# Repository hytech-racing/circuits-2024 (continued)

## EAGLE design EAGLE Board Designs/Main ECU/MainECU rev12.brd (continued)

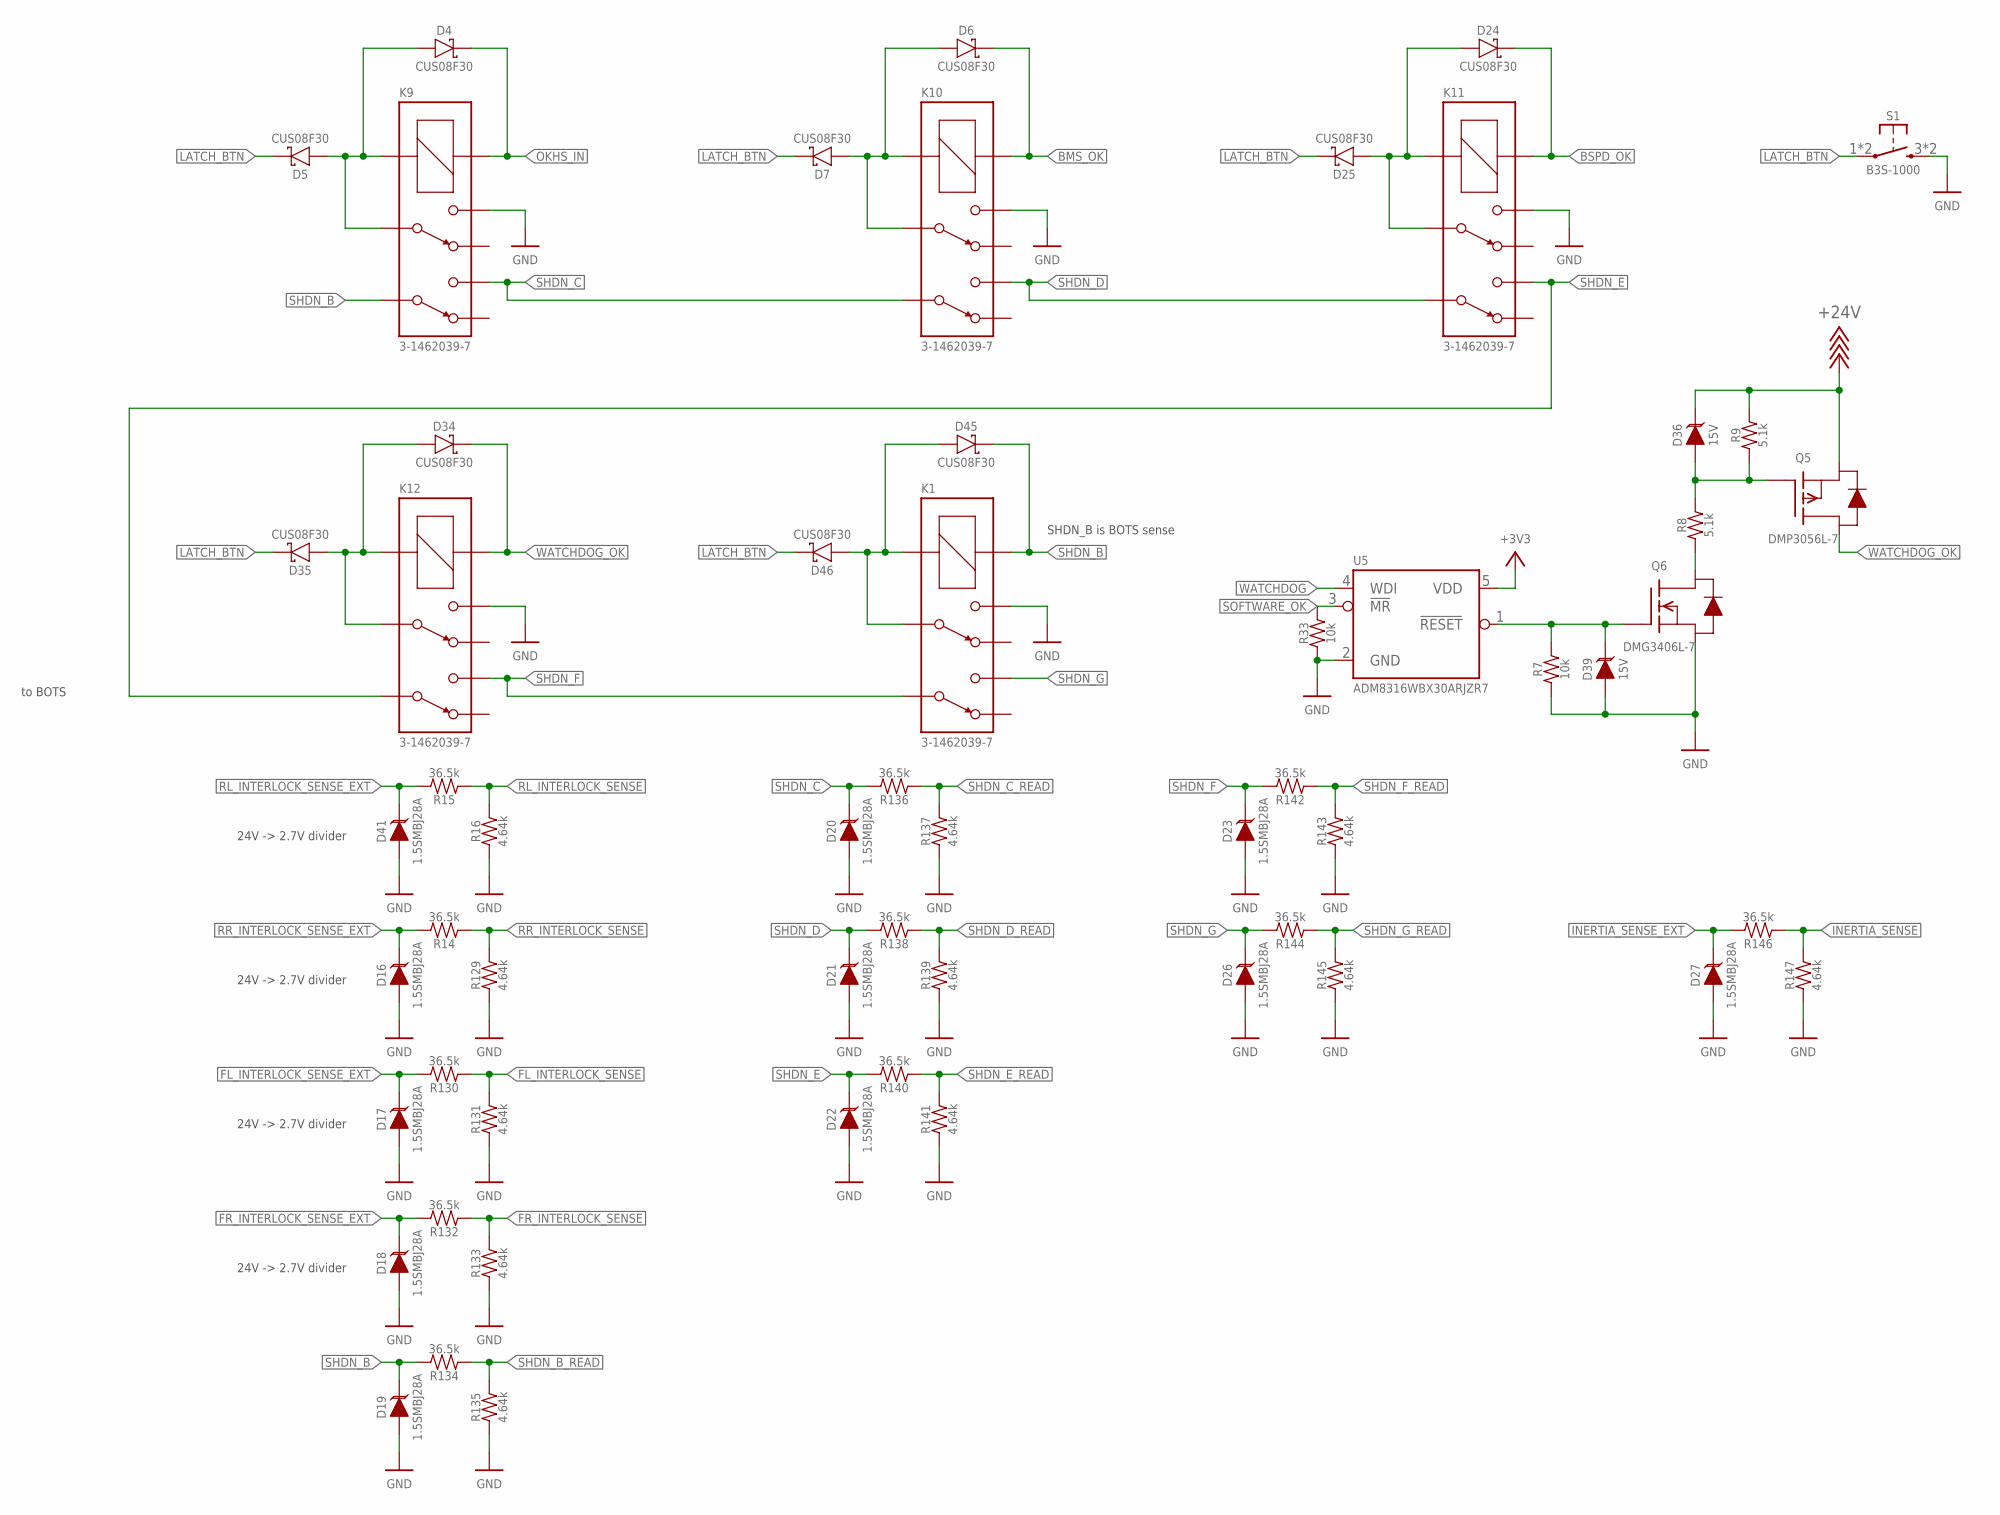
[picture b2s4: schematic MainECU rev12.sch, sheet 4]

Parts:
D4, D5, D6, D7, D24, D25, D34, D35, D45, D46: SCHOTTKY_SOD323_30V; SOD-323
D16, D17, D18, D19, D20, D21, D22, D23, D26, D27, D41: TVS_DO-214AA_28V; DO-214AA
D36, D39: TVS__15V; SOT-23
K1, K9, K10, K11, K12: RELAY_DPDT_07DSMT; IM*G
Q5: TRANSISTOR_P_MOS_SOT-23_DMP3056L-7; SOT-23
Q6: TRANSISTOR_N_MOS__DMG3406L-7; SOT-23
R7, R33: RESISTOR_0603_10K; 0603-RES
R8, R9: RESISTOR_0603_5.1K; 0603-RES
R14, R15, R130, R132, R134, R136, R138, R140, R142, R144, R146: RESISTOR_0603_36.5K; 0603-RES
R16, R129, R131, R133, R135, R137, R139, R141, R143, R145, R147: RESISTOR_0603_4.64K; 0603-RES
S1: BUTTON; B3S-100X
U5: ADM8316WBX30; SOT-23-5

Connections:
+3V3: U5.5 (VDD); also elsewhere on the board
+24V: D36.3 (C), Q5.2 (S), R9.2; also elsewhere on the board
BMS_OK: D6.C, K10.1 (COIL+); also elsewhere on the board
BSPD_OK: D24.C, K11.1 (COIL+); also elsewhere on the board
FL_INTERLOCK_SENSE: R130.1, R131.2; also elsewhere on the board
FL_INTERLOCK_SENSE_EXT: D17.2 (C), R130.2; also elsewhere on the board
FR_INTERLOCK_SENSE: R132.1, R133.2; also elsewhere on the board
FR_INTERLOCK_SENSE_EXT: D18.2 (C), R132.2; also elsewhere on the board
GND: D16.1 (A), D17.1 (A), D18.1 (A), D19.1 (A), D20.1 (A), D21.1 (A), D22.1 (A), D23.1 (A), D26.1 (A), D27.1 (A), D39.1 (A), D41.1 (A), K1.4, K9.4, K10.4, K11.4, K12.4, Q6.2 (S), R7.1, R16.1, R33.1, R129.1, R131.1, R133.1, R135.1, R137.1, R139.1, R141.1, R143.1, R145.1, R147.1, S1.3 (S), S1.4 (S), U5.2 (GND); also elsewhere on the board
INERTIA_SENSE: R146.1, R147.2; also elsewhere on the board
INERTIA_SENSE_EXT: D27.2 (C), R146.2; also elsewhere on the board
LATCH_BTN: D5.C, D7.C, D25.C, D35.C, D46.C, S1.1, S1.2; also elsewhere on the board
unnamed: D36.1 (A), Q5.1 (G), R8.2, R9.1
unnamed: Q6.3 (D), R8.1
unnamed: D4.A, D5.A, K9.3, K9.8 (COIL-)
unnamed: D24.A, D25.A, K11.3, K11.8 (COIL-)
unnamed: D6.A, D7.A, K10.3, K10.8 (COIL-)
unnamed: D45.A, D46.A, K1.3, K1.8 (COIL-)
unnamed: D34.A, D35.A, K12.3, K12.8 (COIL-)
OKHS_IN: D4.C, K9.1 (COIL+); also elsewhere on the board
RL_INTERLOCK_SENSE: R15.1, R16.2; also elsewhere on the board
RL_INTERLOCK_SENSE_EXT: D41.2 (C), R15.2; also elsewhere on the board
RR_INTERLOCK_SENSE: R14.1, R129.2; also elsewhere on the board
RR_INTERLOCK_SENSE_EXT: D16.2 (C), R14.2; also elsewhere on the board
SHDN_B: D19.2 (C), D45.C, K1.1 (COIL+), K9.6, R134.2; also elsewhere on the board
SHDN_B_READ: R134.1, R135.2; also elsewhere on the board
SHDN_C: D20.2 (C), K9.5, K10.6, R136.2; also elsewhere on the board
SHDN_C_READ: R136.1, R137.2; also elsewhere on the board
SHDN_D: D21.2 (C), K10.5, K11.6, R138.2; also elsewhere on the board
SHDN_D_READ: R138.1, R139.2; also elsewhere on the board
SHDN_E: D22.2 (C), K11.5, K12.6, R140.2; also elsewhere on the board
SHDN_E_READ: R140.1, R141.2; also elsewhere on the board
SHDN_F: D23.2 (C), K1.6, K12.5, R142.2; also elsewhere on the board
SHDN_F_READ: R142.1, R143.2; also elsewhere on the board
SHDN_G: D26.2 (C), K1.5, R144.2; also elsewhere on the board
SHDN_G_READ: R144.1, R145.2; also elsewhere on the board
SOFTWARE_OK: R33.2, U5.3 (!MR!); also elsewhere on the board
WATCHDOG: U5.4 (WDI); also elsewhere on the board
WATCHDOG_OK: D34.C, K12.1 (COIL+), Q5.3 (D); also elsewhere on the board
WATCHDOG_OK_LV: D39.3 (C), Q6.1 (G), R7.2, U5.1 (!RESET!)

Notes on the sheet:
to BOTS
24V -> 2.7V divider
SHDN_B is BOTS sense

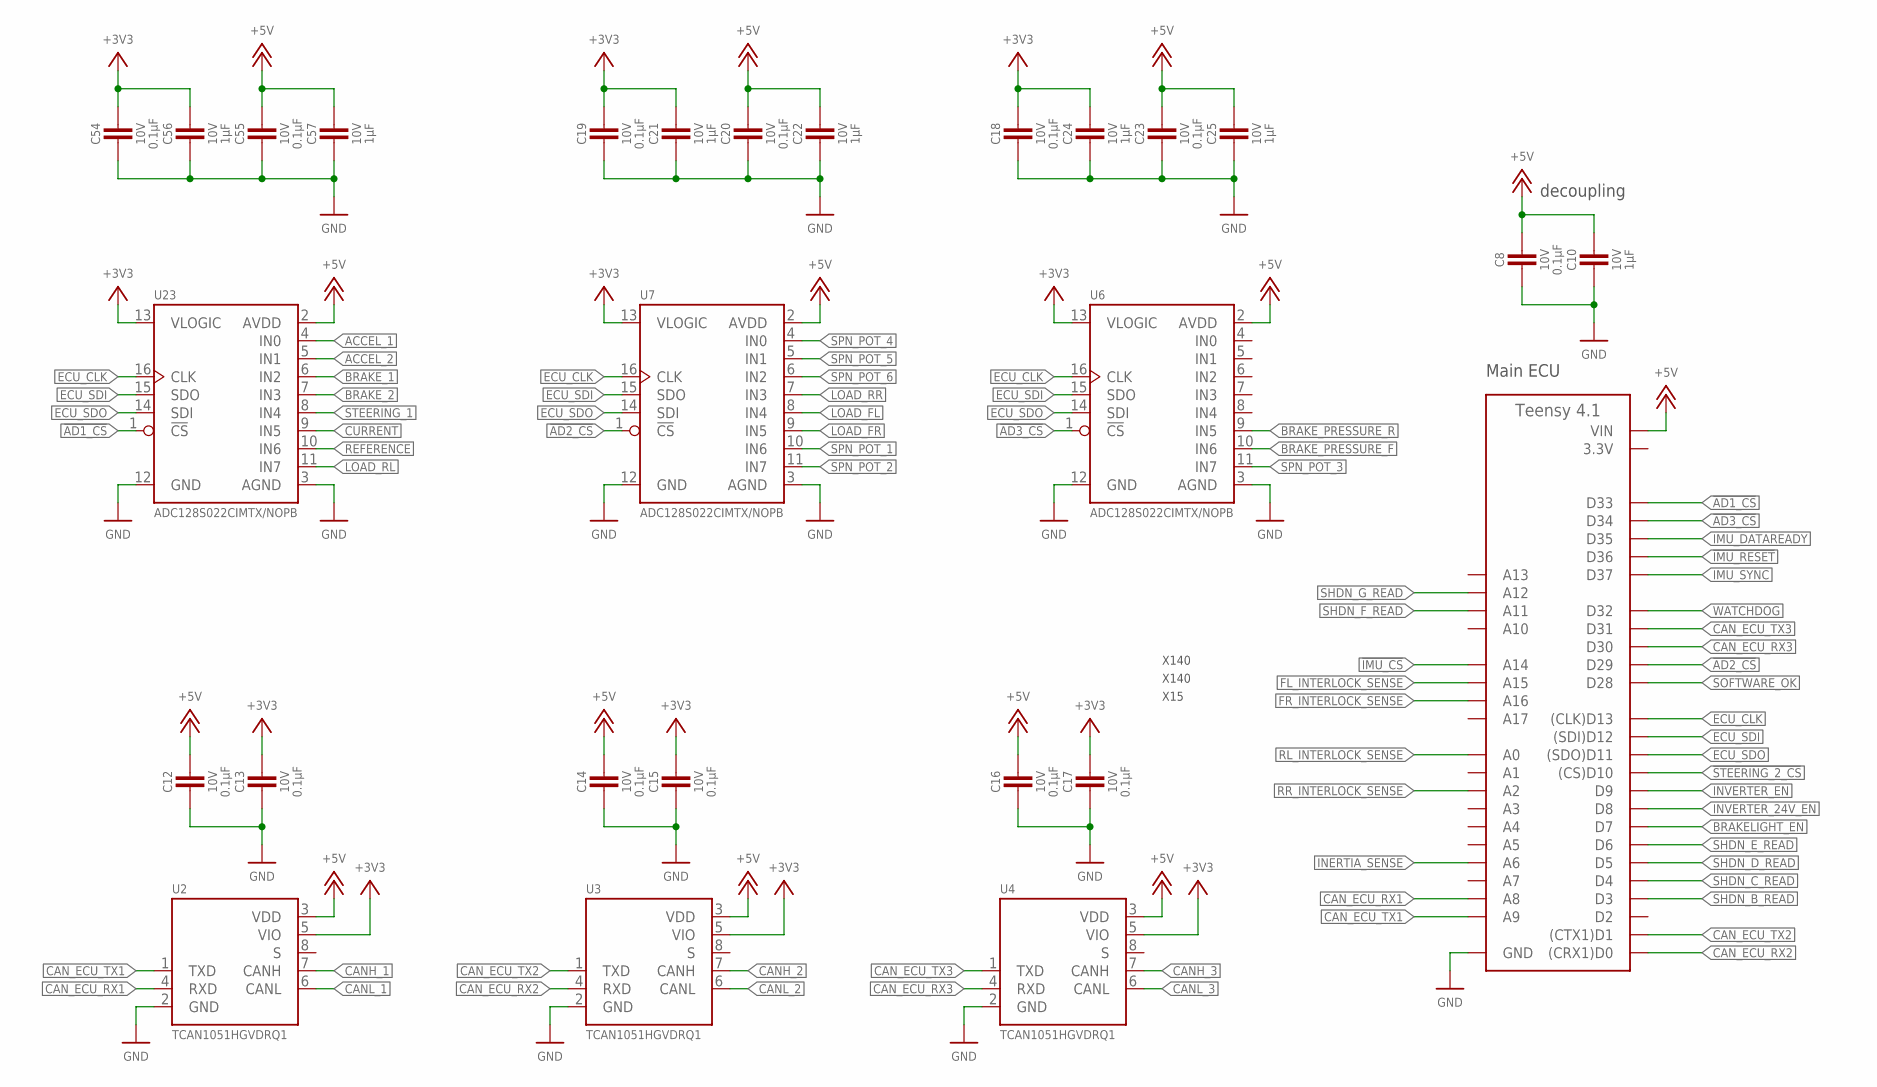
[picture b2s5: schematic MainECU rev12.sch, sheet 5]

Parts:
A2: TEENSY_4.1_SMT; TEENSY_LONG_SSM
C8, C12, C13, C14, C15, C16, C17, C18, C19, C20, C23, C54, C55: CAPACITOR_0603_10V_0.1UF; 0603-CAP
C10, C21, C22, C24, C25, C56, C57: CAPACITOR_0603_10V_1UF; 0603-CAP
U2, U3, U4: TCAN1051HQV-Q1; SOIC-08(NARROW,0.15")
U6, U7, U23: ADC128S022; TSSOP-16

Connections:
3.3V: A2.3.3V, A2.3.3V@1 (3.3V); also elsewhere on the board
!AD1_CS: A2.D33, U23.1 (!CS!)
!AD2_CS: A2.D29, U7.1 (!CS!)
!AD3_CS: A2.D34, U6.1 (!CS!)
!IMU_CS: A2.D38 (A14); also elsewhere on the board
!IMU_RESET: A2.D36; also elsewhere on the board
!STEERING_2_CS: A2.D10 ((CS)D10); also elsewhere on the board
+3V3: C13.1, C15.1, C17.1, C18.1, C19.1, C21.1, C24.1, C54.1, C56.1, U2.5 (VIO), U3.5 (VIO), U4.5 (VIO), U6.13 (VLOGIC), U7.13 (VLOGIC), U23.13 (VLOGIC); also elsewhere on the board
+5V: A2.VIN, C8.1, C10.1, C12.1, C14.1, C16.1, C20.1, C22.1, C23.1, C25.1, C55.1, C57.1, U2.3 (VDD), U3.3 (VDD), U4.3 (VDD), U6.2 (AVDD), U7.2 (AVDD), U23.2 (AVDD); also elsewhere on the board
ACCEL_1: U23.4 (IN0); also elsewhere on the board
ACCEL_2: U23.5 (IN1); also elsewhere on the board
BRAKELIGHT_EN: A2.D7; also elsewhere on the board
BRAKE_1: U23.6 (IN2); also elsewhere on the board
BRAKE_2: U23.7 (IN3); also elsewhere on the board
BRAKE_PRESSURE_F: U6.10 (IN6); also elsewhere on the board
BRAKE_PRESSURE_R: U6.9 (IN5); also elsewhere on the board
CANH_1: U2.7 (CANH); also elsewhere on the board
CANH_2: U3.7 (CANH); also elsewhere on the board
CANH_3: U4.7 (CANH); also elsewhere on the board
CANL_1: U2.6 (CANL); also elsewhere on the board
CANL_2: U3.6 (CANL); also elsewhere on the board
CANL_3: U4.6 (CANL); also elsewhere on the board
CAN_ECU_RX1: A2.D22 (A8), U2.4 (RXD)
CAN_ECU_RX2: A2.D0 ((CRX1)D0), U3.4 (RXD)
CAN_ECU_RX3: A2.D30, U4.4 (RXD)
CAN_ECU_TX1: A2.D23 (A9), U2.1 (TXD)
CAN_ECU_TX2: A2.D1 ((CTX1)D1), U3.1 (TXD)
CAN_ECU_TX3: A2.D31, U4.1 (TXD)
CURRENT: U23.9 (IN5); also elsewhere on the board
ECU_CLK: A2.D13 ((CLK)D13), U6.16 (CLK), U7.16 (CLK), U23.16 (CLK); also elsewhere on the board
ECU_SDI: A2.D12 ((SDI)D12), U6.15 (SDO), U7.15 (SDO), U23.15 (SDO); also elsewhere on the board
ECU_SDO: A2.D11 ((SDO)D11), U6.14 (SDI), U7.14 (SDI), U23.14 (SDI); also elsewhere on the board
FL_INTERLOCK_SENSE: A2.D39 (A15); also elsewhere on the board
FR_INTERLOCK_SENSE: A2.D40 (A16); also elsewhere on the board
GND: A2.AGND/GND (GND), A2.GND, A2.GND@1 (GND), C8.2, C10.2, C12.2, C13.2, C14.2, C15.2, C16.2, C17.2, C18.2, C19.2, C20.2, C21.2, C22.2, C23.2, C24.2, C25.2, C54.2, C55.2, C56.2, C57.2, U2.2 (GND), U3.2 (GND), U4.2 (GND), U6.3 (AGND), U6.12 (GND), U7.3 (AGND), U7.12 (GND), U23.3 (AGND), U23.12 (GND); also elsewhere on the board
IMU_DATAREADY: A2.D35; also elsewhere on the board
IMU_SYNC: A2.D37; also elsewhere on the board
INERTIA_SENSE: A2.D20 (A6); also elsewhere on the board
INVERTER_24V_EN: A2.D8; also elsewhere on the board
INVERTER_EN: A2.D9; also elsewhere on the board
LOAD_FL: U7.8 (IN4); also elsewhere on the board
LOAD_FR: U7.9 (IN5); also elsewhere on the board
LOAD_RL: U23.11 (IN7); also elsewhere on the board
LOAD_RR: U7.7 (IN3); also elsewhere on the board
REFERENCE: U23.10 (IN6); also elsewhere on the board
RL_INTERLOCK_SENSE: A2.D14 (A0); also elsewhere on the board
RR_INTERLOCK_SENSE: A2.D16 (A2); also elsewhere on the board
SHDN_B_READ: A2.D3; also elsewhere on the board
SHDN_C_READ: A2.D4; also elsewhere on the board
SHDN_D_READ: A2.D5; also elsewhere on the board
SHDN_E_READ: A2.D6; also elsewhere on the board
SHDN_F_READ: A2.D25 (A11); also elsewhere on the board
SHDN_G_READ: A2.D26 (A12); also elsewhere on the board
SOFTWARE_OK: A2.D28; also elsewhere on the board
SPN_POT_1: U7.10 (IN6); also elsewhere on the board
SPN_POT_2: U7.11 (IN7); also elsewhere on the board
SPN_POT_3: U6.11 (IN7); also elsewhere on the board
SPN_POT_4: U7.4 (IN0); also elsewhere on the board
SPN_POT_5: U7.5 (IN1); also elsewhere on the board
SPN_POT_6: U7.6 (IN2); also elsewhere on the board
STEERING_1: U23.8 (IN4); also elsewhere on the board
WATCHDOG: A2.D32; also elsewhere on the board

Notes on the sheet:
decoupling
Main ECU
X15
X140

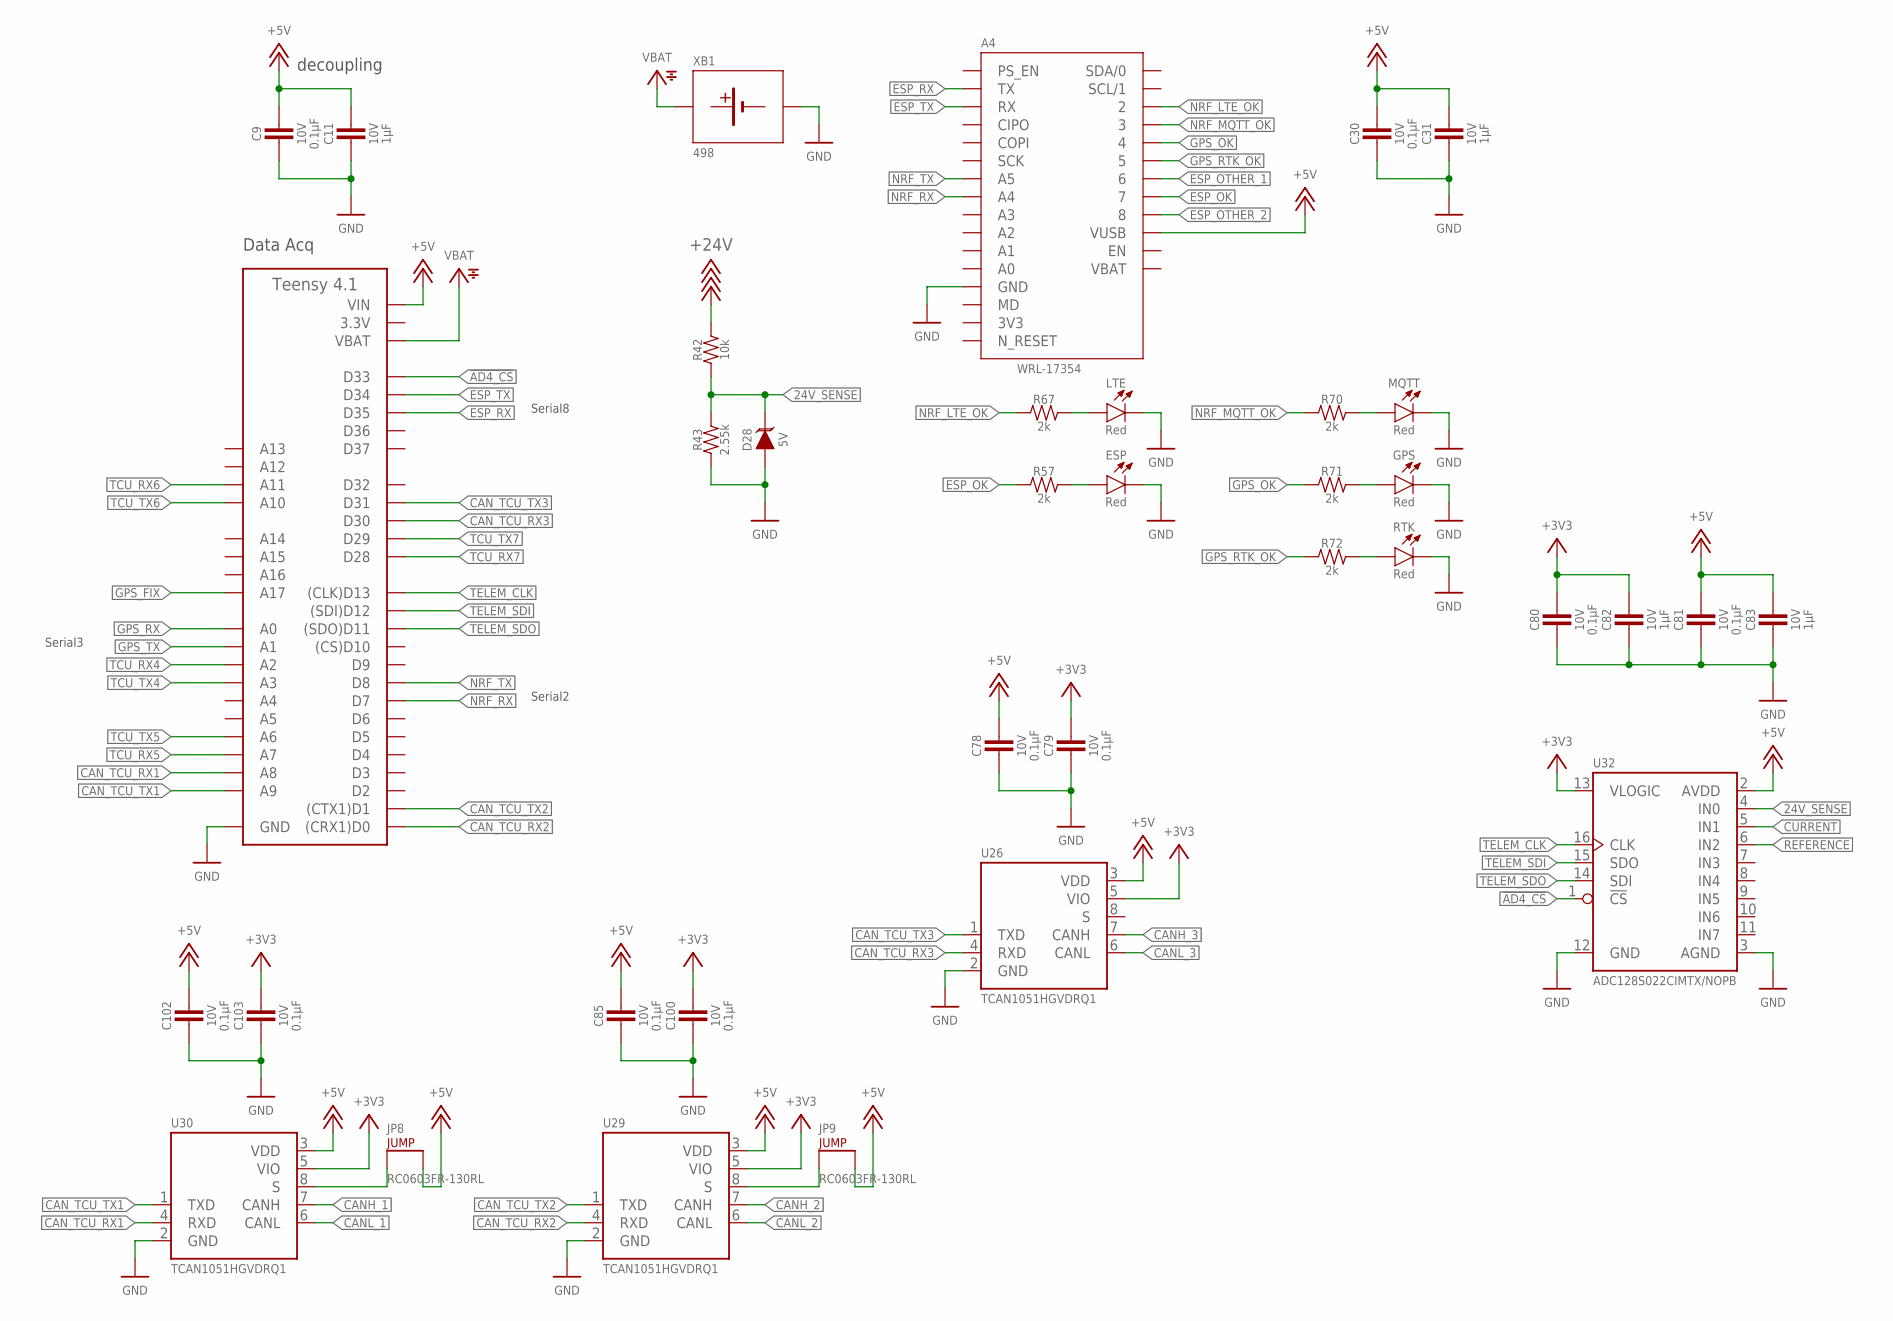
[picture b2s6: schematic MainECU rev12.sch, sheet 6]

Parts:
A3: TEENSY_4.1; TEENSY_LONG_EXT
A4: NRF9160LTE
C9, C30, C78, C79, C80, C81, C85, C100, C102, C103: CAPACITOR_0603_10V_0.1UF; 0603-CAP
C11, C31, C82, C83: CAPACITOR_0603_10V_1UF; 0603-CAP
D28: TVS__5V; SOT-23
ESP: LED_0603_RED; 0603-LED
GPS: LED_0603_RED; 0603-LED
JP8, JP9: JUMPER_0603_; 0603-RES
LTE: LED_0603_RED; 0603-LED
MQTT: LED_0603_RED; 0603-LED
R42: RESISTOR_0603_10K; 0603-RES
R43: RESISTOR_0603_2.55K; 0603-RES
R57, R67, R70, R71, R72: RESISTOR_0603_2K; 0603-RES
RTK: LED_0603_RED; 0603-LED
U26, U29, U30: TCAN1051HQV-Q1; SOIC-08(NARROW,0.15")
U32: ADC128S022; TSSOP-16
XB1: BATTERY_HOLDER_KEYSTONE_498; 498

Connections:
3.3V: A3.3V3 (3.3V), A3.3V3@2 (3.3V), A3.3V3@3 (3.3V); also elsewhere on the board
3V3: A4.3V3
24V_SENSE: D28.3 (C), R42.1, R43.2, U32.4 (IN0)
!AD4_CS: A3.D33, U32.1 (!CS!)
+3V3: C79.1, C80.1, C82.1, C100.1, C103.1, U26.5 (VIO), U29.5 (VIO), U30.5 (VIO), U32.13 (VLOGIC); also elsewhere on the board
+5V: A3.VIN, A4.VUSB, C9.1, C11.1, C30.1, C31.1, C78.1, C81.1, C83.1, C85.1, C102.1, JP8.2, JP9.2, U26.3 (VDD), U29.3 (VDD), U30.3 (VDD), U32.2 (AVDD); also elsewhere on the board
+24V: R42.2; also elsewhere on the board
CANH_1: U30.7 (CANH); also elsewhere on the board
CANH_2: U29.7 (CANH); also elsewhere on the board
CANH_3: U26.7 (CANH); also elsewhere on the board
CANL_1: U30.6 (CANL); also elsewhere on the board
CANL_2: U29.6 (CANL); also elsewhere on the board
CANL_3: U26.6 (CANL); also elsewhere on the board
CAN_TCU_RX1: A3.D22 (A8), U30.4 (RXD)
CAN_TCU_RX2: A3.D0 ((CRX1)D0), U29.4 (RXD)
CAN_TCU_RX3: A3.D30, U26.4 (RXD)
CAN_TCU_TX1: A3.D23 (A9), U30.1 (TXD)
CAN_TCU_TX2: A3.D1 ((CTX1)D1), U29.1 (TXD)
CAN_TCU_TX3: A3.D31, U26.1 (TXD)
CURRENT: U32.5 (IN1); also elsewhere on the board
ESP_OK: A4.7, R57.1
ESP_OTHER_1: A4.6
ESP_OTHER_2: A4.8
ESP_RX: A3.D35, A4.TX
ESP_TX: A3.D34, A4.RX
GND: A3.AGND/GND (GND), A3.GND, A3.GND@2 (GND), A4.GND, C9.2, C11.2, C30.2, C31.2, C78.2, C79.2, C80.2, C81.2, C82.2, C83.2, C85.2, C100.2, C102.2, C103.2, D28.1 (A), ESP.1 (C), GPS.1 (C), LTE.1 (C), MQTT.1 (C), R43.1, RTK.1 (C), U26.2 (GND), U29.2 (GND), U30.2 (GND), U32.3 (AGND), U32.12 (GND), XB1.2 (MINUS); also elsewhere on the board
GPS_FIX: A3.D41 (A17)
GPS_OK: A4.4, R71.1
GPS_RTK_OK: A4.5, R72.1
GPS_RX: A3.D14 (A0)
GPS_TX: A3.D15 (A1)
unnamed: JP8.1, U30.8 (S)
unnamed: JP9.1, U29.8 (S)
unnamed: ESP.2 (A), R57.2
unnamed: LTE.2 (A), R67.2
unnamed: MQTT.2 (A), R70.2
unnamed: GPS.2 (A), R71.2
unnamed: R72.2, RTK.2 (A)
NRF_LTE_OK: A4.2, R67.1
NRF_MQTT_OK: A4.3, R70.1
NRF_RX: A3.D7, A4.A4
NRF_TX: A3.D8, A4.A5
REFERENCE: U32.6 (IN2); also elsewhere on the board
TCU_RX4: A3.D16 (A2)
TCU_RX5: A3.D21 (A7)
TCU_RX6: A3.D25 (A11)
TCU_RX7: A3.D28
TCU_TX4: A3.D17 (A3)
TCU_TX5: A3.D20 (A6)
TCU_TX6: A3.D24 (A10)
TCU_TX7: A3.D29
TELEM_CLK: A3.D13 ((CLK)D13), U32.16 (CLK)
TELEM_SDI: A3.D12 ((SDI)D12), U32.15 (SDO)
TELEM_SDO: A3.D11 ((SDO)D11), U32.14 (SDI)
VBAT: A3.VBAT, A4.VBAT, XB1.1 (PLUS)

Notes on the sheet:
decoupling
Data Acq
Serial2
Serial3
Serial8

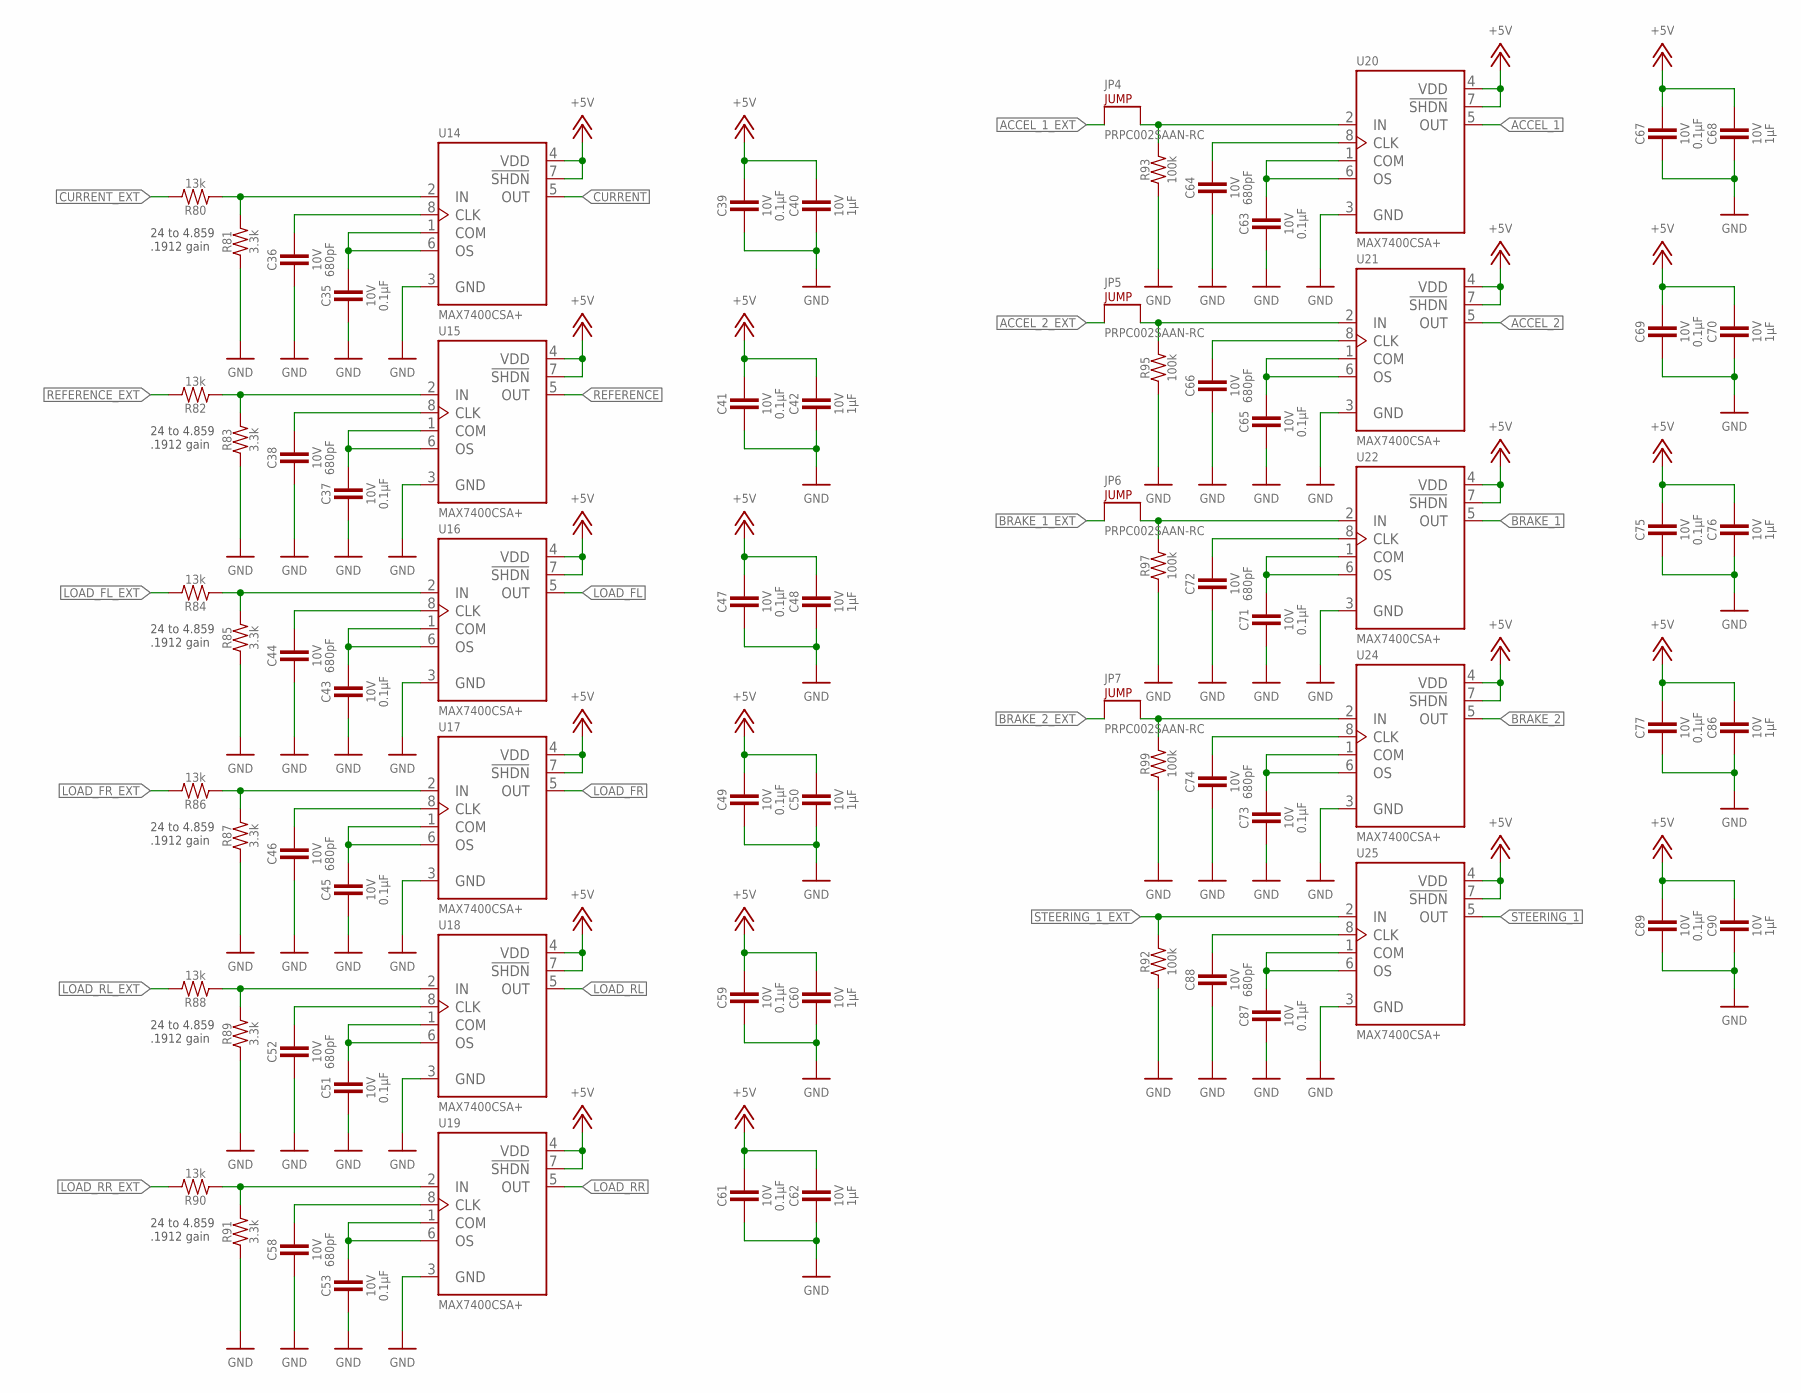
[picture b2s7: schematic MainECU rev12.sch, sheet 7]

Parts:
C35, C37, C39, C41, C43, C45, C47, C49, C51, C53, C59, C61, C63, C65, C67, C69, C71, C73, C75, C77, C87, C89: CAPACITOR_0603_10V_0.1UF; 0603-CAP
C36, C38, C44, C46, C52, C58, C64, C66, C72, C74, C88: CAPACITOR_0603_10V_680PF; 0603-CAP
C40, C42, C48, C50, C60, C62, C68, C70, C76, C86, C90: CAPACITOR_0603_10V_1UF; 0603-CAP
JP4, JP5, JP6, JP7: JUMPER__1X02; 1X02
R80, R82, R84, R86, R88, R90: RESISTOR_0603_13K; 0603-RES
R81, R83, R85, R87, R89, R91: RESISTOR_0603_3.3K; 0603-RES
R92, R93, R95, R97, R99: RESISTOR_0603_100K; 0603-RES
U14, U15, U16, U17, U18, U19, U20, U21, U22, U24, U25: MAX7400; SOIC-08(NARROW,0.15")

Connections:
+5V: C39.1, C40.1, C41.1, C42.1, C47.1, C48.1, C49.1, C50.1, C59.1, C60.1, C61.1, C62.1, C67.1, C68.1, C69.1, C70.1, C75.1, C76.1, C77.1, C86.1, C89.1, C90.1, U14.4 (VDD), U14.7 (!SHDN), U15.4 (VDD), U15.7 (!SHDN), U16.4 (VDD), U16.7 (!SHDN), U17.4 (VDD), U17.7 (!SHDN), U18.4 (VDD), U18.7 (!SHDN), U19.4 (VDD), U19.7 (!SHDN), U20.4 (VDD), U20.7 (!SHDN), U21.4 (VDD), U21.7 (!SHDN), U22.4 (VDD), U22.7 (!SHDN), U24.4 (VDD), U24.7 (!SHDN), U25.4 (VDD), U25.7 (!SHDN); also elsewhere on the board
ACCEL_1: U20.5 (OUT); also elsewhere on the board
ACCEL_1_EXT: JP4.1; also elsewhere on the board
ACCEL_1_PRE: JP4.2, R93.2, U20.2 (IN)
ACCEL_2: U21.5 (OUT); also elsewhere on the board
ACCEL_2_EXT: JP5.1; also elsewhere on the board
ACCEL_2_PRE: JP5.2, R95.2, U21.2 (IN)
BRAKE_1: U22.5 (OUT); also elsewhere on the board
BRAKE_1_EXT: JP6.1; also elsewhere on the board
BRAKE_1_PRE: JP6.2, R97.2, U22.2 (IN)
BRAKE_2: U24.5 (OUT); also elsewhere on the board
BRAKE_2_EXT: JP7.1; also elsewhere on the board
BRAKE_2_PRE: JP7.2, R99.2, U24.2 (IN)
CURRENT: U14.5 (OUT); also elsewhere on the board
CURRENT_EXT: R80.2; also elsewhere on the board
GND: C35.2, C36.2, C37.2, C38.2, C39.2, C40.2, C41.2, C42.2, C43.2, C44.2, C45.2, C46.2, C47.2, C48.2, C49.2, C50.2, C51.2, C52.2, C53.2, C58.2, C59.2, C60.2, C61.2, C62.2, C63.2, C64.2, C65.2, C66.2, C67.2, C68.2, C69.2, C70.2, C71.2, C72.2, C73.2, C74.2, C75.2, C76.2, C77.2, C86.2, C87.2, C88.2, C89.2, C90.2, R81.1, R83.1, R85.1, R87.1, R89.1, R91.1, R92.1, R93.1, R95.1, R97.1, R99.1, U14.3 (GND), U15.3 (GND), U16.3 (GND), U17.3 (GND), U18.3 (GND), U19.3 (GND), U20.3 (GND), U21.3 (GND), U22.3 (GND), U24.3 (GND), U25.3 (GND); also elsewhere on the board
LOAD_FL: U16.5 (OUT); also elsewhere on the board
LOAD_FL_EXT: R84.2; also elsewhere on the board
LOAD_FR: U17.5 (OUT); also elsewhere on the board
LOAD_FR_EXT: R86.2; also elsewhere on the board
LOAD_RL: U18.5 (OUT); also elsewhere on the board
LOAD_RL_EXT: R88.2; also elsewhere on the board
LOAD_RR: U19.5 (OUT); also elsewhere on the board
LOAD_RR_EXT: R90.2; also elsewhere on the board
unnamed: R80.1, R81.2, U14.2 (IN)
unnamed: C35.1, U14.1 (COM), U14.6 (OS)
unnamed: C36.1, U14.8 (CLK)
unnamed: R82.1, R83.2, U15.2 (IN)
unnamed: C37.1, U15.1 (COM), U15.6 (OS)
unnamed: C38.1, U15.8 (CLK)
unnamed: R84.1, R85.2, U16.2 (IN)
unnamed: C43.1, U16.1 (COM), U16.6 (OS)
unnamed: C44.1, U16.8 (CLK)
unnamed: R86.1, R87.2, U17.2 (IN)
unnamed: C45.1, U17.1 (COM), U17.6 (OS)
unnamed: C46.1, U17.8 (CLK)
unnamed: R88.1, R89.2, U18.2 (IN)
unnamed: C51.1, U18.1 (COM), U18.6 (OS)
unnamed: C52.1, U18.8 (CLK)
unnamed: R90.1, R91.2, U19.2 (IN)
unnamed: C53.1, U19.1 (COM), U19.6 (OS)
unnamed: C58.1, U19.8 (CLK)
unnamed: C87.1, U25.1 (COM), U25.6 (OS)
unnamed: C63.1, U20.1 (COM), U20.6 (OS)
unnamed: C64.1, U20.8 (CLK)
unnamed: C88.1, U25.8 (CLK)
unnamed: C65.1, U21.1 (COM), U21.6 (OS)
unnamed: C66.1, U21.8 (CLK)
unnamed: C71.1, U22.1 (COM), U22.6 (OS)
unnamed: C72.1, U22.8 (CLK)
unnamed: C73.1, U24.1 (COM), U24.6 (OS)
unnamed: C74.1, U24.8 (CLK)
REFERENCE: U15.5 (OUT); also elsewhere on the board
REFERENCE_EXT: R82.2; also elsewhere on the board
STEERING_1: U25.5 (OUT); also elsewhere on the board
STEERING_1_EXT: R92.2, U25.2 (IN); also elsewhere on the board

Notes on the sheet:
24 to 4.859 .1912 gain

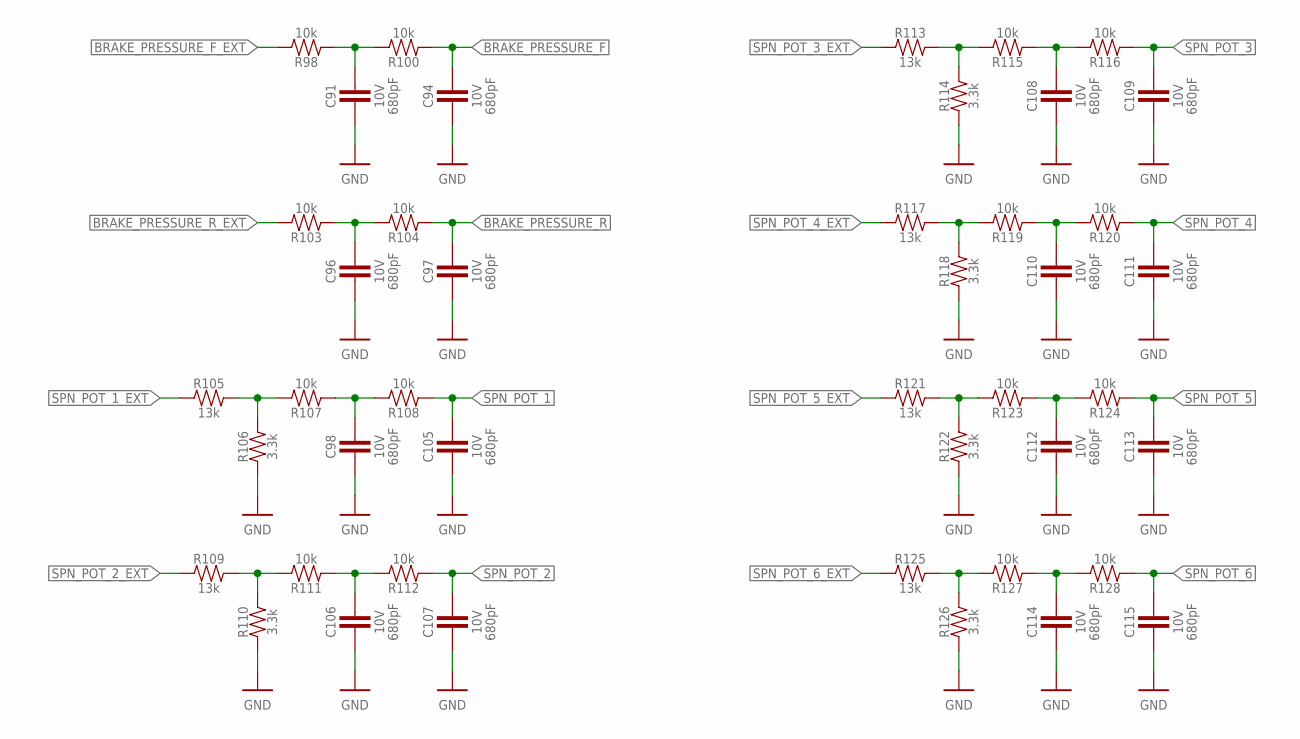
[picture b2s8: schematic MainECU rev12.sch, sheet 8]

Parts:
C91, C94, C96, C97, C98, C105, C106, C107, C108, C109, C110, C111, C112, C113, C114, C115: CAPACITOR_0603_10V_680PF; 0603-CAP
R98, R100, R103, R104, R107, R108, R111, R112, R115, R116, R119, R120, R123, R124, R127, R128: RESISTOR_0603_10K; 0603-RES
R105, R109, R113, R117, R121, R125: RESISTOR_0603_13K; 0603-RES
R106, R110, R114, R118, R122, R126: RESISTOR_0603_3.3K; 0603-RES

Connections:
BRAKE_PRESSURE_F: C94.1, R100.1; also elsewhere on the board
BRAKE_PRESSURE_F_EXT: R98.2; also elsewhere on the board
BRAKE_PRESSURE_R: C97.1, R104.1; also elsewhere on the board
BRAKE_PRESSURE_R_EXT: R103.2; also elsewhere on the board
GND: C91.2, C94.2, C96.2, C97.2, C98.2, C105.2, C106.2, C107.2, C108.2, C109.2, C110.2, C111.2, C112.2, C113.2, C114.2, C115.2, R106.1, R110.1, R114.1, R118.1, R122.1, R126.1; also elsewhere on the board
unnamed: C91.1, R98.1, R100.2
unnamed: C96.1, R103.1, R104.2
unnamed: R105.2, R106.2, R107.2
unnamed: C98.1, R107.1, R108.2
unnamed: R109.2, R110.2, R111.2
unnamed: C106.1, R111.1, R112.2
unnamed: R113.2, R114.2, R115.2
unnamed: C108.1, R115.1, R116.2
unnamed: R117.2, R118.2, R119.2
unnamed: C110.1, R119.1, R120.2
unnamed: R121.2, R122.2, R123.2
unnamed: C112.1, R123.1, R124.2
unnamed: R125.2, R126.2, R127.2
unnamed: C114.1, R127.1, R128.2
SPN_POT_1: C105.1, R108.1; also elsewhere on the board
SPN_POT_1_EXT: R105.1; also elsewhere on the board
SPN_POT_2: C107.1, R112.1; also elsewhere on the board
SPN_POT_2_EXT: R109.1; also elsewhere on the board
SPN_POT_3: C109.1, R116.1; also elsewhere on the board
SPN_POT_3_EXT: R113.1; also elsewhere on the board
SPN_POT_4: C111.1, R120.1; also elsewhere on the board
SPN_POT_4_EXT: R117.1; also elsewhere on the board
SPN_POT_5: C113.1, R124.1; also elsewhere on the board
SPN_POT_5_EXT: R121.1; also elsewhere on the board
SPN_POT_6: C115.1, R128.1; also elsewhere on the board
SPN_POT_6_EXT: R125.1; also elsewhere on the board
